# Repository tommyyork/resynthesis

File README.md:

# Resynthesis

This example implements a resynthesis effect for the Electro-Smith Daisy Patch.Init(), initially inspired by [the All Electric Smart Grid project](https://github.com/jvictor0/theallelectricsmartgrid) but it grew towards a granular direction as I added additional processing / while iterating on the output sounds. **This is maybe 90% GPT (🤖), 10% human, so buyer beware if you fork this or use this code.** There are plenty of bugs.

The panel design has most of the development hours, I wanted to procedurally generate it from the KiCad files for Patch.Init():

I've sent this off to the fab, and will make any updates once I've test fitted it on my actual Patch.Init(). Those labels for the pots may be too low...

The panel generation code could pretty easily be adapted to generate panels for any synth module, though the drill diameters and tolerances are currently hardcoded and basically tailored for the jacks / pots / switches you see in many Eurorack modules. The background pattern-to-pattern interpolation... I wish I could take credit. See [the agent session](AGENT_SESSION.md) for the blow by blow on how that came to be.

Incoming audio is analyzed into overlapping FFT grains, processed spectrally (phase propagation, V/OCT pitch, spectral flattening, bright/dark tilt, sparsity, and phase diffusion), and resynthesized with overlap-add back to the output. The V/OCT input (0–10 V) sets the fundamental frequency so the module can be used as an oscillator in a bass patch.

### Offline tests vs hardware signal path

The offline tests under `test/` are designed for **analysis and regressions**, not for level‑matched listening against the live module:

- **V/OCT harmonic tests (`make voct`, `test/test_resynth_voct.cpp`)**  
  - The processed passes are rendered **100% wet** with **no dry mix, no compressor, and no soft clip**.  
  - Grains are normalized only by hop size and active‑grain count, which keeps the **internal DSP stable** but typically yields WAVs that are **much quieter than the dry input**.  
  - This is intentional: the goal is **stable spectra and reliable note detection** (CSV/SVG analysis, suggested‑note checks), not loudness parity with the original sample or with the hardware output.

- **Harmonic engine tests (`make samples` → `test_resynth_harmonic`, `out/harmonic/*.wav`)**  
  - These also run the simplified harmonic resynth engine **fully wet** without the Patch‑SM output chain (no OFFER dry path, no post‑clip compressor, no panel‑driven MAX COMP).  
  - As a result, the harmonic test WAVs can also sit **significantly below** the level of the source material even though the spectra and pitch tracking match the intended behaviour.

- **Hardware firmware (`Resynthesis.cpp`)**  
  - On the Daisy Patch SM, the same core engine is wrapped in a **full output path**: OFFER dry/wet crossfade, hop/overlap‑aware wet gain smoothing, **smoothing‑dependent loudness compensation**, **soft clipping**, and a **fixed compressor/optional MAX COMP** stage.  
  - This chain is where the “finished instrument” loudness lives; the offline tests intentionally **omit** it so they can focus on **spectral behaviour, pitch stability, and CV‑to‑pitch mapping**.

If you A/B the `make voct` / harmonic WAVs against the original samples or the hardware output, expect them to be **significantly quieter**; treat them as **analysis fixtures**, not as loudness‑matched renderings of the module.

## Title: 化 (huà)

The panel uses the single character **化** (*huà*) as its primary title, from the *Daodejing* (道德經) in the sense of **transformation**—the change of one state into another, as in the phrase **化而欲作** (*huà ér yù zuò*, “when transformation arises, desire stirs”; ch. 37). Here it evokes the transformation of incoming sound through the phase vocoder into new timbres and textures.

**Panel typography:** All panel text is set in **all caps** using the open-source DIN-style font **[Gidole](https://github.com/larsenwork/Gidole)** (OFL licence; also available via [Google Fonts](https://fonts.google.com/specimen/Gidole)). The SVG uses the `Gidole` font family with fallbacks (DIN Alternate, DIN 2014, sans-serif) so the panel renders correctly even if Gidole is not installed.

## Make Targets

- **`make` / `make all`**: Build everything for this project (no tests are run): `libDaisy`, `DaisySP`, the `Resynthesis` firmware, host test binaries in `test/`, panel preview PNGs, and the SVG/PDF block‑diagram documentation.
- **`make program`**: Flash the built firmware image to the connected Daisy Patch SM.
- **`make openocd`**: Start OpenOCD for JTAG/SWD debug sessions.
- **`make debug`**: Build a debug firmware image and launch a GDB session against OpenOCD (with logging enabled as described below).
- **`make panel`**: Generate high‑resolution PNG previews of the front‑panel art in `panel/ResynthesisPanel.png` and `panel/ResynthesisPanel_eurorack_overlay.png` (requires Inkscape).
- **`make svg`**: Generate the US Letter block diagram of the audio path in `doc/Resynthesis_BlockDiagram_USLetter.pdf` and `doc/Resynthesis_BlockDiagram_USLetter.svg` (requires Graphviz `dot`).
- **`make test_resynth`**: Build and run the offline V/OCT sweep test; outputs WAVs into `test/out/voct_sweep/`.
- **`make test_cv_sweeps`**: Build and run the CV parameter sweep tests; outputs WAVs into `test/out/cv_sweep/` and `test/out/cv_sweep_maxcomp/`.
- **`make test_panel`**: Run the panel alignment / mechanical checks in `panel/test_panel_alignment.py`.
- **`make tests`**: Run the full test suite (`test_resynth`, `test_cv_sweeps`, and `test_panel`), regenerating WAVs under `test/out/`.
- **`make clean`**: Remove build artifacts and generated assets for this project (host test binaries, `test/out` WAVs, panel PNGs, and block‑diagram PDF/SVG/DOT files).

## Controls and panel mapping

This section is the **source of truth for panel labels and control behaviour**. Labels assume the **default CV bank** (no swapping).

### Potentiometers (CV_1–CV_4)

- **CV_1 – OFFER – send + dry/wet (panel: `OFFER`)**  
  Combined send and mix control for the resynthesis engine. **Fully CCW**, the output is **purely dry input** (non‑pitch‑shifted), and the engine effectively stops seeding new grains, so if no grains are currently active you hear a clean bypass. As you turn toward **12 o’clock**, the input is increasingly **“offered” to the grain engine** while a crossfade brings in the wet signal; around noon you get roughly **half dry, half wet** with the input actively feeding grains. **Fully CW** behaves like a **full send into the resynth path** so the output is dominated by loud, fully wet grains.  
  When **PITCH LOCK is on**, OFFER additionally becomes a **“pitch crossfade”**: CCW you hear the original, unshifted input; CW you hear a **clearly pitched, harmonically focused granular reconstruction** whose fundamental and partials follow the V/OCT voltage and **COLOR** setting, with most of the grain energy collapsing onto those harmonic families. Sweeping OFFER from CCW → CW in this case moves smoothly from dry, unshifted audio into the **fully pitch‑shifted, harmonically reinforced voice**, while existing grains are still allowed to **decay naturally** when you come back toward CCW.

- **CV_2 – Time‑Stretch / Grain Density (panel: `TIMESTRETCH`)**
  Bipolar control around 1× time. This knob controls how quickly grains are launched relative to the analysis hop: **left of centre** slows down and smears the audio into super‑slow, cloud‑like textures, while **right of centre** increases grain density and motion up into fast, chattery clusters. The mapping mirrors the TIME CV input so that the **0 V / noon region** covers the most musically useful 0.25×–4× range, with more extreme slow/fast behaviour toward the ends of travel.

- **CV_3 – FLUFF – granular cloud depth (panel: `FLUFF`)**  
  Sequentially enables a set of increasingly strong “cloud” behaviours in the grains. **Fully CCW** gives the most subtle, stable sound. As you turn clockwise, the engine adds:  
  1. Extra frequency‑dependent phase diffusion on top of CV_8.  
  2. Random jitter of the analysis window within each grain (time smearing) for a denser cloud.  
  3. Micro‑pitch jitter per grain in **pitch‑locked mode** (a few cents of movement around the target note).  
  4. Per‑bin magnitude jitter for a noisy, dense cloud at fully CW.  
  Existing spectral‑energy normalization keeps level changes musical across settings.

- **CV_4 – Color – bright/dark tilt, harmonic & frequency character (panel: `COLOR`)**  
  Three roles:
  - **Spectral tilt:** Negative values darken (emphasize low bins), positive values brighten (emphasize high bins); tilt gain is clamped so extremes do not clip or go silent.  
  - **Harmonic character in both modes (whenever PITCH LOCK is on):** **Color** selects which harmonic family is reinforced in **both** pitch‑locked and partial‑based modes using a **12‑harmonic scaffold** built on the V/OCT fundamental. **Fully CCW** emphasises the **even harmonics** \(2nd, 4th, 6th, … up to 12th\); around **noon** you get a more neutral mix; near **3 o’clock** and beyond the scaffold leans harder into the **odd harmonics**. Power is **front‑loaded into the low harmonics** and then tapered so that roughly the first four harmonics carry most of the added energy and higher harmonics contribute a progressively smaller, more textural sheen. In pitch‑locked mode the scaffold is gentler so the pitched grains stay dominant; in partial‑based mode the scaffold is more forward so simple inputs behave like a full synth voice. Reinforced partials use moderate, tapered gains so they **blend with the resynthesized body** rather than sounding like separate oscillators.  
  - **Pitch vs frequency shifting crossfade:** With PITCH LOCK on, the audio now passes through a dedicated **shifting block** immediately after the input. This block first **detects the incoming pitch** using a harmonic‑comb analyser (refactored from the offline V/OCT tests) and **pitch‑shifts** the input so its fundamental lands on the V/OCT‑selected note *before* any phase‑vocoder processing. As COLOR moves from roughly **3 o’clock to fully CW**, the block smoothly **fades from this pitch‑shifting process into a Bode‑style frequency shifter** whose shift rate also follows V/OCT. Fully CW gives a distinctly **frequency‑shifted, sideband‑style texture** feeding the resynth engine; backing off toward 3 o’clock restores more of the classic pitch‑locked behaviour.

### Toggles (B_7, B_8)

- **B_8 – PITCH LOCK (panel: `PITCH` / `LOCK`)**  
  Mode switch between **pitch‑locked grains** and a **partial‑based spectral model**:
  - **B_8 off – Partial‑based / spectral model mode**: Treats the incoming spectrum as a timbral template. Analysis bins stay at their original pitch; a **harmonic scaffold** (fundamental + harmonics) tuned to the **V/OCT** fundamental is overlaid with moderate gain so simple inputs behave like a full synth voice. **Color (CV_4)** selects the balance of odd vs even harmonics.  
  - **B_8 on – Pitch‑locked grains**: The phase‑vocoder pitch shifter locks each grain so its spectrum follows the V/OCT fundamental. This behaves more like a traditional pitched oscillator with the input acting as a complex waveform; the **same harmonic scaffold** is now applied more gently on top, reinforcing the chosen harmonic family without overwhelming the pitch‑corrected grains.

- **B_7 – MAX COMP (panel: `MAX` / `COMP`)**  
  Toggles a **stronger “MAX COMP” output compressor** after the resynth engine:
  - **Hardware:** B_7 is a **momentary pushbutton**, but the firmware treats it as a **software toggle**: each press flips the MAX COMP state between off and on.  
  - **B_7 off – Normal compression**: A gentle **2:1 feedforward compressor** (threshold ≈ -12 dB, modest make‑up gain) keeps levels musical and consistent as a sound source without being too squashy.  
  - **B_7 on – MAX COMP**: A more aggressive **Omnipressor‑style setting** (negative ratio, higher make‑up gain) that keeps average loudness high and brings out quiet material; this matches the “MAX COMP” path used in the offline CV sweep tests (`test/out/cv_sweep_maxcomp/`). When MAX COMP is active, the **front‑panel status LED above the jacks blinks at roughly 1 Hz** to indicate that the software toggle is engaged.

### CV inputs (CV_5–CV_8, middle jack row)

The middle jack row (panel labels above the jacks) is:

- `V/OCT`, `SMOOTH`, `SPARSITY`, *`D`* (diffusion)

Mapped controls:

- **CV_5 – V/OCT (panel: `V/OCT`, 0–10 V, 1 V/oct)**  
  Volt‑per‑octave pitch control. In both modes the algorithm resynthesizes the input around a musical fundamental set by this voltage (e.g. 1 V ≈ 32.7 Hz / C1, 2 V ≈ 65.4 Hz / C2). In **pitch‑locked mode** the new **shifting block** and the phase‑vocoder engine both treat this as the target note: the block first **shifts the raw input** so its detected fundamental lands on the requested V/OCT pitch, and the phase‑vocoder then follows that same fundamental when mapping grains; in **partial‑based mode** the original spectrum stays nearer its analysed pitch while a more forward harmonic scaffold (fundamental + harmonics) is overlaid at the V/OCT frequency.  
  With PITCH LOCK on and OFFER turned up, the combination of the shifting block and harmonic scaffold now **focuses most of the spectral energy into the fundamental and harmonics implied by V/OCT and COLOR** so the result is a **grainy but clearly pitched voice** rather than a diffuse, purely formant‑style texture. At the very top of COLOR, that same V/OCT value instead drives the **frequency‑shift amount** in the Bode‑style shifter, giving inharmonic, sideband‑rich tones feeding the resynth stage. 0 V = C0 (~16.35 Hz); 10 V is internally clamped near the upper range.

- **CV_6 – Magnitude Smoothing (panel: `SMOOTH`, bipolar, -5 V to +5 V)**  
  Controls how quickly spectral magnitudes follow the input. **Low** voltages track transients closely (crisp, articulate); **high** voltages smear dynamics into a pad‑like magnitude envelope. The engine’s **default** smoothing is now around **0.2**, which keeps transients present while still allowing the adaptive smoothing stages to build a stable, cloud‑like body at higher settings.

- **CV_7 – Spectral Sparsity (panel: `SPARSITY`, bipolar, -5 V to +5 V)**  
  Bipolar control mapped to the full **0–1** sparsity range (0 V ≈ 0.5). Lower values keep most bins active and sound fuller; higher values keep only the strongest bins, leading to more pronounced, metallic / ring‑mod‑like spectra, with internal energy preservation so results stay present rather than simply “thin”.

- **CV_8 – Phase Diffusion (panel: italic `D`, bipolar, -5 V to +5 V)**  
  Bipolar control mapped to the full **0–1** diffusion range (0 V ≈ 0.5). Lower values keep phases more coherent (clearer tone); higher values introduce strong randomization for noisy, cloud‑like, frequency‑shift‑ish textures. **FLUFF (CV_3)** can add extra diffusion on top of this control.

### CV outputs (CV_OUT_1, CV_OUT_2)

- **CV_OUT_1 / C10 – THOUGHTS (panel: lightning bolt symbol `⚡`)**  
  CV jack directly beneath the COLOR knob (top‑right of the middle‑switch/jack cluster).  
  - **Signal:** A **chaotic, Brownian‑like CV** that wanders in a musically bounded way between 0–5 V. Its motion becomes **wider and quicker** when the input is loud and harmonically rich, and **slower and more restrained** when the input is quieter and more noise‑like or spectrally flat.  
  - **Construction:** Internally, THOUGHTS is driven by a **logistic‑map–style chaotic system**. Each audio frame, the engine measures both a smoothed spectral‑energy value and a simple **harmonic peakiness metric** (how “spiky” the spectrum is relative to its mean). These two features form an **excitement** value that modulates the chaotic map’s parameter and effective step rate, then the result is centered, range‑scaled by excitement, and gently low‑pass filtered before being mapped to 0–5 V.  
  - **Musical uses:** Because THOUGHTS reacts to both loudness and harmonic structure but with an internal chaotic drift, it behaves as an **interesting, somewhat tangential CV source**: ideal for slowly moving filter cutoffs, effect depths, wavefolder thresholds, or other processors that you want to “breathe” with the resynth texture without being a simple envelope follower. High‑energy, harmonic material produces animated, complex CV excursions; sparse or dark inputs yield smaller, slower meanders that still feel alive.

- **CV_OUT_2 – Grain energy meter + MAX COMP status / LED driver (no dedicated panel label)**  
  Drives the **front‑panel status LED** (row “LED (status)” in the jack/part mapping table) and exposes a **0–5 V envelope of the grain engine’s activity**, with a **MAX COMP blink overlay**:  
  - **Base behaviour (MAX COMP off):** CV_OUT_2 follows the current **grain / spectral energy** of the resynthesis engine, mapped into **0–5 V**. Quiet, sparse material produces a dim LED / low CV; louder, denser inputs push the LED and CV level towards 5 V.  
  - **MAX COMP on (software toggle engaged):** The same grain‑energy envelope continues to drive CV_OUT_2, but a **logic‑style overlay blinks the output at full intensity (~1.5 Hz)** to show that MAX COMP is active. During the “on” phase of the blink the output is forced to **5 V**; during the “off” phase it returns to the underlying grain‑energy level.  
  This output is intended primarily for the on‑panel LED, but you can patch it elsewhere either as a **grain‑energy envelope follower** or as a **MAX COMP activity indicator**. Its behaviour is independent of **THOUGHTS (CV_OUT_1)**, which continues to carry the separate chaotic CV derived from the same internal analysis.

### Jacks: gates, CVs, and audio I/O

Panel jack layout (from top row to bottom row; labels are **over** each jack and centered):

- **Top row** (4 jacks): `B10`, `B9`, `B5`, `B6` — gate inputs/outputs.
- **Middle row** (4 jacks): `V/OCT` (CV_5), *`t`* / TIME (CV_6), `SPARSITY` (CV_7), *`D`* / diffusion (CV_8).
- **Bottom row** (4 jacks): `IN L`, `IN R`, `OUT L`, `OUT R` — stereo audio inputs and outputs. The two middle jacks are also **CV_OUT_1** and **CV_OUT_2** in firmware.

### Stereo inputs and outputs

- **IN L / IN R (bottom row, left two jacks; panel: `IN L`, `IN R`)**  
  Audio inputs mapped to firmware channels `IN_L` and `IN_R`. They feed the analysis stage of the phase vocoder; typical use is a stereo source (e.g. a loop, synth, or external instrument).

- **OUT L / OUT R (bottom row, right two jacks; panel: `OUT L`, `OUT R`)**  
  Audio outputs mapped to firmware channels `OUT_L` and `OUT_R`. Carry the fully processed resynth signal after shaping, overlap‑add synthesis, soft clipping, and final compressor. Useful both as **effect returns** and as a standalone stereo sound source when driven from V/OCT.

## Panel

### Files

- **`panel/output/ResynthesisPanel.svg`**  
  Vector artwork of a 3U x 10HP Eurorack panel: height **128.5 mm**, width **50.8 mm**. All graphics and drill holes are in millimetres. **Generated by** `panel/_deprecated_generate_panel.py` (or `panel/generate_panel_kicad.py`).

- **`panel/output/ResynthesisPanel.jpg`**  
  Single panel preview image for quick visual reference. Generated from `ResynthesisPanel.svg` by `make panel` (requires Inkscape).

- **`panel/output/render_eurorack_overlay.py`**  
  Script that generates an **Eurorack standard overlay** SVG from any panel SVG: green dotted 2HP vertical grid, neon blue dotted rail‑center lines, neon pink (x, y) annotations at each cut center plus panel dimensions.

- **`panel/_deprecated_generate_panel.py`**  
  Deprecated Python script that generates the canonical `ResynthesisPanel.svg` (prefer `panel/generate_panel_kicad.py`). It encodes the full 3U × 10HP geometry, background artwork, all drill centres, the SD card holder cutout, and the four rectangular Eurorack mounting screw slots so they line up with the Doepfer / Gie‑Tec rail standard (3 mm from the top and bottom edges; see `panel/eurorack_spec/README.md`).

### Input / jack mapping (KiCad PCB → panel)

The table below ties together the **Resynthesis panel labels**, the **Patch.Init default panel silkscreen**, the **KiCad schematic references**, and the mechanical information from the KiCad footprints. Positions are given in KiCad PCB coordinates (millimetres) taken from `panel/KiCad_PCB/ES_Daisy_Patch_SM_FB_Rev1.kicad_pcb`.

| Resynthesis label   | Patch.Init panel label | Component type          | Panel hole Ø (mm) | PCB X (mm) | PCB Y (mm) | KiCad schematic ref | Footprint filename                  |
|---------------------|------------------------|-------------------------|-------------------|------------|------------|----------------------|-------------------------------------|
| B10 (gate in 1)     | B10                    | S_JACK                  | 6.2               | 130.251    | 125.316    | J_GATEIN1            | `S_JACK.kicad_mod`                  |
| B9 (gate in 2)      | B9                     | S_JACK                  | 6.2               | 142.418    | 125.316    | J_GATEIN2            | `S_JACK.kicad_mod`                  |
| B5 (gate out 1)     | B5                     | S_JACK                  | 6.2               | 154.584    | 125.316    | J_GATEOUT1           | `S_JACK.kicad_mod`                  |
| B6 (gate out 2)     | B6                     | S_JACK                  | 6.2               | 166.751    | 125.316    | J_GATEOUT2           | `S_JACK.kicad_mod`                  |
| V/OCT               | CV_5                   | S_JACK                  | 6.2               | 130.251    | 139.065    | J_CV1                | `S_JACK.kicad_mod`                  |
| SMOOTH              | CV_6                   | S_JACK                  | 6.2               | 142.418    | 139.065    | J_CV2                | `S_JACK.kicad_mod`                  |
| SPARSITY            | CV_7                   | S_JACK                  | 6.2               | 154.584    | 139.065    | J_CV3                | `S_JACK.kicad_mod`                  |
| D (diffusion)       | CV_8                   | S_JACK                  | 6.2               | 166.751    | 139.065    | J_CV4                | `S_JACK.kicad_mod`                  |
| IN L                | IN_L / B4              | S_JACK                  | 6.2               | 130.251    | 152.654    | J_LIN1               | `S_JACK.kicad_mod`                  |
| IN R                | IN_R / B3              | S_JACK                  | 6.2               | 142.418    | 152.654    | J_RIN1               | `S_JACK.kicad_mod`                  |
| OUT L               | OUT_L / B2             | S_JACK                  | 6.2               | 154.584    | 152.654    | J_LOUT1              | `S_JACK.kicad_mod`                  |
| OUT R               | OUT_R / B1             | S_JACK                  | 6.2               | 166.751    | 152.654    | J_ROUT1              | `S_JACK.kicad_mod`                  |
| THOUGHTS            | CV_OUT_1 / C10         | S_JACK                  | 6.2               | 165.251    | 100.036    | J_CVOUT1             | `S_JACK.kicad_mod`                  |
| LED (status)        | LED_1                  | LED                     | 3.2               | 148.501    | 60.128     | LED_1                | `LED.kicad_mod`                     |
| MAX COMP (B_7)      | B7 / SW_1              | TL1105SPF250Q_SILK      | 5.5               | 131.751    | 100.036    | SW_1                 | `TL1105SPF250Q_SILK.kicad_mod`      |
| PITCH LOCK (B_8)    | B8 / SW_2              | TOGGLE_ON-ON            | 6.2               | 148.501    | 102.786    | SW_2                 | `TOGGLE_ON-ON.kicad_mod`            |
| microSD slot        | —                      | VERT_MICROSD_CENTERED   | — (rectangular cutout) | 148.501    | 80.855     | U_SDCARD1            | `VERT_MICROSD_CENTERED.kicad_mod`   |
| OFFER (CV_1)        | CV_1 / C5              | 9MM_SNAP-IN_POT_SILK    | 7.2               | 134.251    | 63.756     | VR_1                 | `9MM_SNAP-IN_POT_SILK.kicad_mod`    |
| SMOOTH (CV_2)       | CV_2 / C4              | 9MM_SNAP-IN_POT_SILK    | 7.2               | 162.751    | 63.756     | VR_2                 | `9MM_SNAP-IN_POT_SILK.kicad_mod`    |
| FLUFF (CV_3)        | CV_3 / C3              | 9MM_SNAP-IN_POT_SILK    | 7.2               | 134.251    | 82.865     | VR_3                 | `9MM_SNAP-IN_POT_SILK.kicad_mod`    |
| COLOR (CV_4)        | CV_4 / C2              | 9MM_SNAP-IN_POT_SILK    | 7.2               | 162.751    | 82.865     | VR_4                 | `9MM_SNAP-IN_POT_SILK.kicad_mod`    |

For all jacks, the panel hole diameter is derived from the **S_JACK** KiCad footprint by measuring the outer silkscreen circle at the footprint origin, which reflects the mechanical body / shaft size of the jack that the panel must clear.

### Manufacturing notes

- The SVG uses **mm** for size and coordinates. Most PCB CAD tools can import this as a mechanical layer to generate Gerbers for:
  - Board outline (the outer rectangle)
  - Drill holes (circle centres and radii for jacks, knobs, switches, and mounting holes)
  - **SD card holder cutout** (rectangular cutout matching Patch.Init Edge_Cuts)
  - Silkscreen (text and decorative shapes)
- For a PCB front panel:
  - Use at least **1.6 mm** FR4 for stiffness (or thicker if desired).
  - Put the artwork on the **front silkscreen** and any copper artwork on the **front copper** layers as desired.
  - Make sure to align the drill centres with your chosen hardware footprints (jacks, pots, switches) in your CAD tool before fabrication.

### Panel drill alignment and tests

Earlier iterations of this panel were laid out by eye against the hardware, which meant the **drill locations and diameters did not exactly match** the stock Electrosmith Patch.Init front panel.

The current `panel/ResynthesisPanel.svg` has been revised so that:

- The board outline is **50.8 × 128.5 mm** (10HP × 3U), matching `panel/patch_init_gerbers/blank-Edge_Cuts.gbr`.
- There are **exactly 22 drill holes**, matching the non‑plated NPTH tools in `panel/patch_init_gerbers/blank-NPTH.drl`:
  - 2 × 3.0 mm mounting holes (implemented on the panel as four wide rectangular screw slots whose equivalent 3.0 mm drill centres match the Patch.Init NPTH file and sit 3 mm from the top and bottom edges, per the Eurorack rail standard),
  - 1 × 3.2 mm (T2) for the front‑panel status LED,
- 1 × 5.5 mm (T3) for the **TL1105… / TOGGLE_ON‑ON** toggle switch at B_7 (MAX COMP),
  and 1 × 6.2 mm (sharing the jack-family tool) for the PITCH LOCK toggle at B_8,
  - 1 × 6.2 mm (T4) for the **TL1105… / TOGGLE_ON‑ON** toggle switch at B_8 (PITCH LOCK), sharing the jack-family diameter for additional clearance,
  - 13 × 6.2 mm (T4) for **S_JACK…** audio/CV jacks and gate I/O,
  - 4 × 7.2 mm (T5) for **9MM_SNAP‑IN_POT…** potentiometer shafts.
- A rectangular **SD card holder cutout** is present and matches `panel/patch_init_gerbers/blank-Edge_Cuts.gbr` (position and size within 0.1 mm).
- Hole positions are matched within **0.05 mm** to the NPTH drill file. The **final panel hole diameters** for pots (9MM_SNAP‑IN_POT…), switches (TL1105… / TOGGLE_ON‑ON at B_7 and the PITCH LOCK toggle at B_8), and jacks (S_JACK…) are derived in `panel/_deprecated_generate_panel.py` (and `panel/generate_panel_kicad.py`) from the NPTH drill diameters in `blank-NPTH.drl`, with a small per‑family clearance so the checked‑in artwork (7.5 mm pots, 5.5 mm B_7 switch, 6.3 mm jacks/B_8 switch) remains the single source of truth for the cut‑out geometry while still tracking any future changes to the drill file. The PITCH LOCK / B_8 toggle uses the jack-family 6.2 mm drill (T4) for its panel cutout so the white outline ring encircles the full clearance hole.

The helper script `panel/test_panel_alignment.py` enforces that any panel design passes the tests. Key tests:

- **`test_panel_drill_holes_match_patch_init`** – Verifies that the canonical panel SVG has drill hole positions and diameters identical to `blank-NPTH.drl` (tight tolerances).  
- **`test_custom_panels_align_with_canonical`** – Any alternate `ResynthesisPanel_*.svg` must share the same hardware hole layout as the canonical panel.  
- **`test_canonical_panel_dimensions_and_diameters`** – Checks dimensions, viewBox, and internal consistency of hole radii; confirms Patch.Init PTH drill file is metric.  
- **`test_panel_cutouts_four_pots_switches_and_sd_slot_match_patch_init`** – Confirms pot, switch, and SD‑slot cutouts are present and aligned with the Patch.Init module.  
- **`test_screw_holes_eurorack_rail_distance`** – Verifies that rectangular screw slots are 3 mm from top and bottom edges (Eurorack rails).  
- **`test_panel_passes_pcbway_style_validation`** – Runs PCBWay‑style mechanical checks (min hole size, spacing, hole‑to‑edge, board dimensions).  
- **`test_knob_labels_not_obscured_by_rogan_knobs`** – Ensures Rogan‑style knobs (12 mm) with 0.5 mm clearance do not cover the primary labels (`DRY / WET`, `SMOOTH`, `FLUFF`, `BRIGHT /`).  
- **`test_no_overlapping_text`**, **`test_text_within_printed_area`**, **`test_no_font_smaller_than_10pt`**, **`test_labels_beneath_drill_centered`** – Typography/layout guards so the panel remains legible and mechanically sane.

### External references and expected file formats

External mechanical references and design rules:

- **Eurorack / Doepfer A-100 mechanical standard** – summarized in `panel/eurorack_spec/README.md` (mounting hole positions, panel height, links to Doepfer and other docs).  
- **Patch.Init blank front‑panel Gerbers** – including `blank-NPTH.drl` and `blank-Edge_Cuts.gbr`, used as the mechanical reference.  
- **PCBWay design‑rule documentation** – sets conservative minimums for hole size, spacing, and hole‑to‑edge clearance, as enforced by the tests.

## Instructions

1. **Initialize submodules**:
   ```bash
   git submodule update --init --recursive
   ```
2. **Build the project (normal / release)**:
   ```bash
   make
   ```
3. **Program the device (optional)**:
   ```bash
   make program
   ```

4. **Debug build with JTAG/serial logging (optional)**:
   - Start OpenOCD in one terminal:
     ```bash
     make openocd
     ```
   - In another terminal, build and start a debug session:
     ```bash
     make debug
     ```
   In debug builds the firmware enables Daisy’s logger and:
   - Prints the startup values of all CV_1–CV_8 inputs and the states of switches B_7 and B_8.
   - Periodically prints diagnostic information while audio runs (active grains, spectral energy, current control values, etc.) over the JTAG/serial link.

5. **Run offline V/OCT sample render (optional)**:
   - **Purpose:** The test runs the phase vocoder resynthesis so that the **output length equals the duration of the V/OCT CV movement**: **14 quarter notes at 120 BPM** (7 seconds). The input is truncated or zero-padded to exactly that length. A simulated **V/OCT CV** (0–10 V) steps **once per quarter note** through **two diatonic octaves** (14 steps). **Dry/wet is fixed at 100% wet**. Other parameters use **musical defaults** (smoothing ≈ 0.4, flatten = 0, tilt = 0, sparsity ≈ 0.2, diffusion ≈ 0.2, time scale = 1.0).
   - **Samples:** Place **48 kHz** WAV(s) in `test/samples/`. The test runs for **every WAV** in that folder (no fixed filenames). Outputs go to **`test/out/voct_sweep/`** with names **`<basename>_voct_sweep.wav`** (e.g. `chromaplane_voct_sweep.wav`, `dryseq_voct_sweep.wav`).
  - From the Resynthesis (project) root:
  ```bash
  make samples
  ```
   - **V/OCT CV movement:** The test drives the resynth’s pitch as a volt-per-octave CV (0–10 V) that steps every quarter note at 120 BPM across **two octaves in one pass** (7 s). If you use a sample that requires attribution, add it to the **Attribution** section below.

6. **Run CV parameter sweep renders (optional)**:
   - **Purpose:** For each CV parameter, process the input with that parameter swept across a **musical range of timbres** while the others sit at a slightly bright, low‑sparsity, low‑diffusion “glassy” neutral. Dry/wet is swept 0% → 100% wet **only** in the first test; all other sweeps run at 100% wet. **Default V/OCT is 2 V (C2)** for all sweeps except the V/OCT test. The V/OCT sweep (CV_5) now uses the **sample itself as input** and is **quantized over three octaves (1 V→4 V)** so you hear clear note steps instead of a pure glide. Each set of sweeps is rendered **twice**: once in **pitch‑locked mode** and once in the **partial‑based / spectral‑model mode**. **Four output directories** are used:
     - **`test/out/cv_sweep/`** — CV sweeps **without** MAX COMP in **pitch‑locked mode** (equivalent to **B_7 off** on hardware). One file per parameter per sample: `<basename>_cv1_offer_feed.wav`, `<basename>_cv2_timestretch.wav`, … `<basename>_cv8_phase_diffusion.wav`.
     - **`test/out/cv_sweep_maxcomp/`** — Same sweeps **with** MAX COMP in **pitch‑locked mode** (equivalent to **B_7 on**); each output is checked to have average level **> -60 dBFS**.
     - **`test/out/cv_sweep_partial/`** — CV sweeps **without** MAX COMP in **partial‑based / spectral‑model mode**.
     - **`test/out/cv_sweep_maxcomp_partial/`** — CV sweeps **with** MAX COMP in **partial‑based / spectral‑model mode**.
   - **Samples:** Same as the offline test: **every 48 kHz WAV** in `test/samples/` is processed (e.g. `chromaplane.wav`, `dryseq.wav`). Output names: **`<basename>_cv1_offer_feed.wav`**, **`<basename>_cv2_timestretch.wav`**, **`<basename>_cv3_flatten.wav`**, **`<basename>_cv4_tilt.wav`**, **`<basename>_cv5_voct.wav`** (V/OCT 1 V→4 V over 30 s, sample‑driven and quantized over three octaves), **`<basename>_cv6_smoothing.wav`**, **`<basename>_cv7_sparsity.wav`**, **`<basename>_cv8_phase_diffusion.wav`**. Across the full set of sweeps and both modes, the rendered WAVs move from **clear, glassy resynth tones** at low settings into **harmonically rich, formant‑heavy and cloud‑like textures** at the high end.
  - From the Resynthesis root:
  ```bash
  make samples
  ```

7. **Run FLUFF granular sample renders (optional)**:
   - **Purpose:** Demonstrate how the **FLUFF** control sounds as it is swept across its full range, both with and without V/OCT. For each 48 kHz WAV in `test/samples/`, the test plays the sample **twice**:
     - **First repetition:** FLUFF is swept from **0 → 1** over the length of the sample with **no V/OCT movement** (fixed fundamental, as if the V/OCT jack were unpatched).
     - **Second repetition:** The sample is played again with FLUFF swept **0 → 1** over the second pass while a **diatonic scale from 2 V to 3 V** (one octave, major scale) is spread evenly across the entire length of that second repetition.
   - Outputs go to **`test/out/fluff/`** with names **`<basename>_fluff_sweep.wav`**.
  - From the Resynthesis root:
  ```bash
  make samples
  ```
8. **Run automated property tests (non-audio, recommended for CI)**:
  - **Purpose:** Quickly exercise the core resynthesis engine on synthetic input to guard against obvious stability issues (e.g. NaNs/Infs, gross clipping) without generating WAVs.
  - From the Resynthesis root:
  ```bash
  make tests
  ```

## Design notes for recent DSP changes

- **Smoothing ≈ 0.2 for musicality**: Early versions used ~0.3–0.4 as a neutral smoothing value. After refining the adaptive smoothing curves and loudness compensation, a **lower base smoothing (~0.2)** keeps transients clearer while the activity‑dependent smoothing still builds a stable, pad‑like envelope at higher knob and CV settings. This makes the effect feel more open and less smeared at default, while still reaching glassy extremes when desired.
- **Sparsity and diffusion back to 0–1 (with safeguards)**: The bipolar -5 V..+5 V range now maps to **0–1** for both sparsity and phase diffusion (0 V ≈ 0.5), restoring strong ring‑mod / frequency‑shift‑like metallic effects when desired. Spectral‑energy preservation, grain normalization, and tilt‑gain clamping keep these extremes loud and present rather than simply “thin” or silent.
- **Tilt gain clamping**: The bright/dark tilt originally allowed very large boosts/cuts at the top and bottom of the spectrum, which in practice caused clipping or near‑silence in edge cases (e.g. the `church_bells_cv4_tilt.wav` sweep). Internally, tilt gain is now clamped to a moderate range so full‑scale CV sweeps remain usable while still clearly changing timbre.
- **Spectral energy preservation**: After flatten/tilt/sparsity have been applied in the spectral domain, the total energy is renormalized to closely match the pre‑shaping energy. This reduces level jumps when turning controls and makes the resynth output easier to mix.
- **Grain overlap normalization and soft clip**: Wet grains are normalized by the number of active grains plus hop size so the overall level stays similar whether 1 or several grains overlap. A gentle soft clip on the output catches remaining peaks without harsh distortion, again aiming for a more stable and musical perceived loudness.
- **Fixed compressor (last stage)**: After the soft clip, a feedforward compressor with fixed settings runs so the output is **louder and more consistent** as a sound source for a filter and amplitude (e.g. VCF/VCA). Threshold ≈ -12 dB, ratio 2:1, fast attack (~0.3 ms), medium release (~50 ms), and make-up gain so the resynthesized signal sits at a useful level. This avoids the need to crank downstream gain and evens out dynamics so the module works well as an oscillator or texture source. *Alternative considered:* updating the algorithm so output volume closely follows input volume (e.g. envelope-following gain on the wet path); the compressor was chosen for fixed behaviour, predictable level, and one less dependency on input dynamics.
- **Grain launch jitter (“spray”)**: Grain launch timing is dithered around the nominal hop size (±30%), both on hardware and in the offline / CV sweep tests. This breaks the perfectly regular launch grid so grains overlap in a more scattered, “alien” way while still roughly tracking the requested time‑stretch factor.
-
- **CV sweep timbre coverage (glassy → formant‑heavy)**: The CV sweep tests are voiced so that, taken together, they span a wide range of timbres from **clear, glassy tones** to **harmonically rich, formant‑heavy spectra**:
  - The default sweep “neutral” is slightly bright, low‑sparsity, low‑diffusion, yielding a clean glassy resynth tone when parameters are near their minima.
  - **Smoothing** sweeps from a fast, transient‑friendly value (~0.10) up to a very slow value (~0.95), moving from crisp transient tracking into highly smeared, glass‑like pads.
  - **Flatten** sweeps from a mostly original spectrum (≈0.10) to fully whitened (1.0), making formant peaks and harmonic reinforcement stand out at the high end.
  - **COLOR (tilt) and SPARSITY** sweeps exercise the **harmonic scaffold in both modes**: in pitch‑locked mode the scaffold adds gentle, keyboard‑tracked formants on top of the pitch‑corrected grains; in partial‑based / spectral‑model mode it becomes more dominant, so the odd/even families selected by COLOR produce dense, formant‑style resonances instead of just “thinner” spectra.
  - **Phase diffusion** sweeps from coherent phases (clear tone) to strong diffusion (noisy / cloud‑like textures), with existing energy‑preserving and normalization stages keeping both extremes musically usable in the rendered test WAVs.
- **FLUFF (granular cloud depth)**:
  - The **FLUFF** control is implemented as **four sequential stages**, each adding more granular character while preserving overall level via existing spectral‑energy normalization:
    1. **Extra phase diffusion**: Adds a small, frequency‑dependent phase randomisation on top of CV_8, starting subtly at low FLUFF settings. This softens phase coherence and reduces small pops without washing out the spectrum.
    2. **Analysis‑window jitter**: Shifts each grain’s FFT window slightly forward/backward in the rolling input history. This creates time‑smeared grains and a denser “cloud” from the same source material.
    3. **Micro‑pitch jitter (pitch‑locked mode only)**: In pitch‑locked mode (B_8 on), each grain’s pitch ratio is perturbed by a few cents (amount grows with FLUFF). The result is a shimmering, animated cluster around the nominal V/OCT pitch while remaining clearly in tune.
    4. **Per‑bin magnitude jitter**: At high FLUFF settings, small random gain variations are applied per spectral bin before synthesis (with energy preservation and clamps). This adds a noisy, granular halo to the sound, especially obvious with sustained inputs.

- **Pitch‑locked vs partial‑based modes**: The phase‑vocoder engine exposes a simple mode flag:
- **Pitch‑locked grains (B_8 on):** The global pitch ratio is applied to all bins so grains follow V/OCT directly; a **gentle harmonic scaffold** reinforces the chosen odd/even family from **Color**, keeping the overall feel that of “pitch‑corrected grains with musical formants”. In this mode, with **V/OCT patched and OFFER high**, most grain energy is pulled toward the harmonic series so the sound reads as a **clearly pitched, harmonically rich resynth voice**.
- **Partial‑based / spectral model (B_8 off):** The original spectrum remains at its analysed pitch; a **stronger harmonic bank** tuned to the V/OCT fundamental (with odd/even balance from **Color**) is multiplied into the spectrum, turning simple sources into full, harmonically rich synth voices while still allowing more inharmonic / noisy content to sit between the reinforced partials.

## Attribution (test audio)

The tests use input WAV(s) from `test/samples/`. If you use royalty-free samples that require attribution, add them here. Example for BBC content:

- **Test input sample:** *Church bells* from [BBC Sound Effects](https://sound-effects.bbcrewind.co.uk/), © BBC, used under the [RemArc licence](https://sound-effects.bbcrewind.co.uk/licensing). Used as input to the phase vocoder resynthesis in this project’s test suite.

**Suggested source:** [BBC Sound Effects](https://sound-effects.bbcrewind.co.uk/) — search for “church bells”, “bells”, or “cathedral”; download a clip and convert to 48 kHz WAV if needed. BBC Sound Effects are made available under the [RemArc licence](https://sound-effects.bbcrewind.co.uk/licensing) for personal, educational or research use. Place 48 kHz WAV(s) in `test/samples/`; the tests run for every WAV in that folder.

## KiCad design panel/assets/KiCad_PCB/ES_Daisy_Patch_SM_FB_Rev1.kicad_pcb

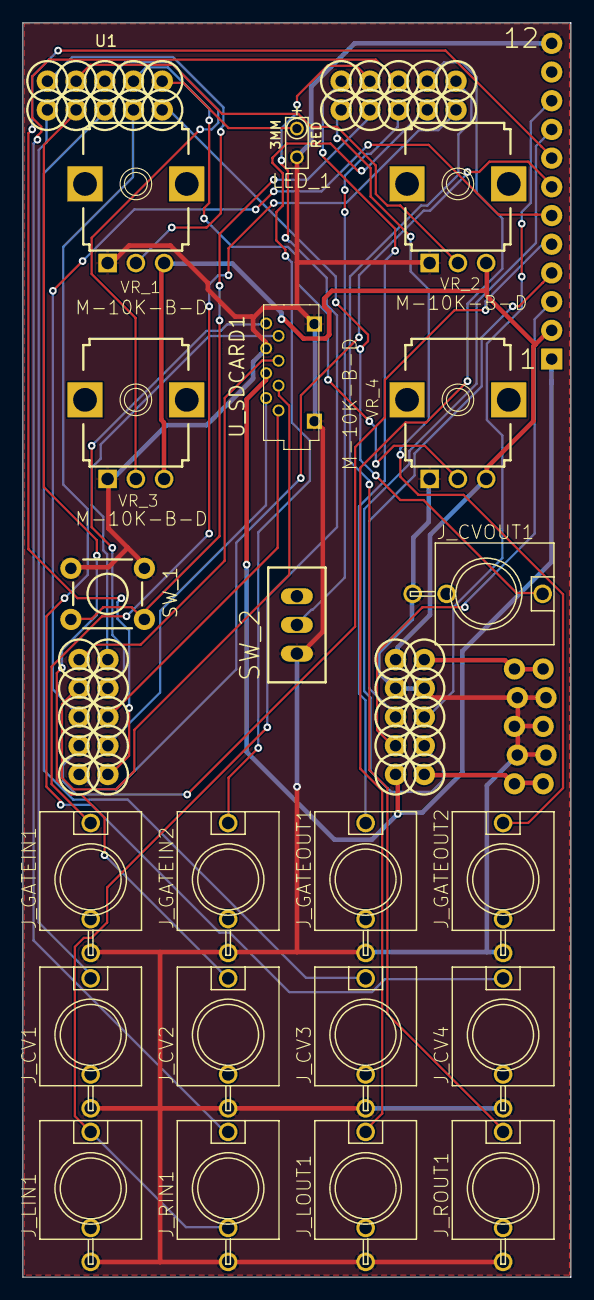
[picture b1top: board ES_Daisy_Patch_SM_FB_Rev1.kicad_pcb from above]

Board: 2 copper layers, 48.5 x 111.0 mm, 26 parts (0 on the bottom side), 39 nets.

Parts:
EP1: EURORACK_POWERLOCK; EURORACK_POWER_SHROUD_LOCK
J_CV1, J_CV2, J_CV3, J_CV4: EURO_JACK; S_JACK
J_CVOUT1: EURO_JACK; S_JACK
J_GATEIN1, J_GATEIN2: EURO_JACK; S_JACK
J_GATEOUT1, J_GATEOUT2: EURO_JACK; S_JACK
J_LIN1: EURO_JACK; S_JACK
J_LOUT1: EURO_JACK; S_JACK
J_RIN1: EURO_JACK; S_JACK
J_ROUT1: EURO_JACK; S_JACK
LED_1: LED
LOGO1: ELECTROSMITH_CIRCLE_4.5MM; ES_CIRCLE_4.5MM
P1: M12; 1X12
SW_1: minibutton; TL1105SPF250Q_SILK
SW_2: TOGGLE_ON-ON
U1: ES_DAISY_PATCH_SM_REV1
U$2: DAISYLOGO; ES_DAISY_LOGO_1
U_SDCARD1: MICRO_SD_CARDCENTERED; VERT_MICROSD_CENTERED
VR_1, VR_2, VR_3, VR_4: M-10K-B-D; 9MM_SNAP-IN_POT_SILK

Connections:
+3V3: P1.1, U1.A10, U_SDCARD1.P$4
+5V: P1.2, U1.A6, VR_1.3, VR_2.3, VR_3.3, VR_4.3
+12V: EP1.POS1, EP1.POS2, U1.A5
-12V: EP1.NEG1, EP1.NEG2, U1.A1
/SD_CK: U1.D6, U_SDCARD1.P$5
/SD_CMD: U1.D7, U_SDCARD1.P$3
/SD_D0: U1.D5, U_SDCARD1.P$7
/SD_D1: U1.D4, U_SDCARD1.P$8
/SD_D2: U1.D3, U_SDCARD1.P$1
/SD_D3: U1.D2, U_SDCARD1.P$2
/SIG_CV1: J_CV1.TIP, U1.C6
/SIG_CV2: J_CV2.TIP, U1.C7
/SIG_CV3: J_CV3.TIP, U1.C8
/SIG_CV4: J_CV4.TIP, U1.C9
/SIG_CVOUT1: J_CVOUT1.TIP, U1.C10
/SIG_CVOUT2: LED_1.A, U1.C1
/SIG_GATE_IN_1: J_GATEIN1.TIP, U1.B10
/SIG_GATE_IN_2: J_GATEIN2.TIP, U1.B9
/SIG_GATE_OUT_1: J_GATEOUT1.TIP, U1.B5
/SIG_GATE_OUT_2: J_GATEOUT2.TIP, U1.B6
/SIG_KNOB1: U1.C5, VR_1.2
/SIG_KNOB2: U1.C4, VR_2.2
/SIG_KNOB3: U1.C3, VR_3.2
/SIG_KNOB4: U1.C2, VR_4.2
/SIG_LIN: J_LIN1.TIP, J_RIN1.NORM, U1.B4
/SIG_LOUT: J_LOUT1.TIP, U1.B2
/SIG_RIN: J_RIN1.TIP, U1.B3
/SIG_ROUT: J_ROUT1.TIP, U1.B1
/SIG_SPI_MISO: P1.6, U1.D8
/SIG_SPI_MOSI: P1.5, U1.D9
/SIG_SPI_NSS: P1.8, U1.D1
/SIG_SPI_SCK: P1.7, U1.D10
/SIG_SW1: SW_1.1, SW_1.2, U1.B7
/SIG_SW2: SW_2.2, U1.B8
/SIG_UART_RX: P1.9, U1.A2
/SIG_UART_TX: P1.10, U1.A3
/SIG_USB_DM: P1.4, U1.A8
/SIG_USB_DP: P1.3, U1.A9
GND: EP1.GND1, EP1.GND2, EP1.GND3, EP1.GND4, EP1.GND5, EP1.GND6, J_CV1.GND, J_CV2.GND, J_CV3.GND, J_CV4.GND, J_CVOUT1.GND, J_GATEIN1.GND, J_GATEIN2.GND, J_GATEOUT1.GND, J_GATEOUT2.GND, J_LIN1.GND, J_LOUT1.GND, J_RIN1.GND, J_ROUT1.GND, LED_1.K, P1.12, SW_1.3, SW_1.4, SW_2.1, U1.A4, U1.A7, U_SDCARD1.GND1, U_SDCARD1.GND2, U_SDCARD1.P$6, VR_1.1, VR_2.1, VR_3.1, VR_4.1

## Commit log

2026-03-05 Resynthesis: adaptive smoothing, MAX COMP routing, and test updates
    - Raise the floor and reshape the CV_2 smoothing response so the panel’s 12 o’clock position is a musical “sweet spot”, concentrating the fastest/grittiest behaviour into the top of the control range.
    - Make magnitude smoothing adaptive to both spectral loudness and harmonic peakiness so dense, excited material automatically smooths into a cloud instead of abrasive static, while simpler inputs rem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
    - Add time‑stretch‑aware smoothing so extreme slow/fast `time_scale` settings get extra smoothing, reducing chatter in `_cv6_timestretch` and related MAX COMP examples without dulling normal operatio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
    -
2026-03-05 Resynthesis: refine sparsity, harmonic stack, and FLUFF renders
    - Tweak spectral sparsity shaping and band‑tilt so high CV values produce more animated, clustered textures while low values behave like gentle density shaping
    - Strengthen V/OCT harmonic scaffold, focusing, and level management so pitched use cases read more clearly without runaway gain
    - Add Makefile fluff target and retune FLUFF test defaults for smoother dynamics and more neutral baseline renders
    Made-with: Cursor
2026-03-05 fix to makefile.
2026-03-05 Resynthesis: retune smoothing and swap TIMESTRETCH/SMOOTH CVs
    Lower default magnitude smoothing to ~0.2, move TIMESTRETCH to CV_2 and SMOOTH to CV_6 across firmware, tests, docs, and panel generator so panel, CV sweeps, and block diagram stay in sync.
    Made-with: Cursor
2026-03-05 Resynthesis: add shifting block and align voct tests
    Add a Shifting front-end that pitch- and frequency-shifts input when PITCH LOCK is on, including a tracking high-pass just below the V/OCT fundamental, and document it in the block diagram and README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
    Made-with: Cursor
2026-03-05 Resynthesis: clarify offline tests and voct stack
    Tie the V/OCT harmonic-stack behaviour more tightly to pitch-locked mode so the requested fundamental dominates suggested-note analysis in the offline voct tests, while keeping the partial-based mode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
    Made-with: Cursor
2026-03-05 Note in the readme that this has moved more granular.
2026-03-06 Refactor - LLM may have screwed up the audio path.
2026-03-06 add taesg as inspiration.
2026-03-07 readme update.
2026-03-07 Panel: KiCad generator, mount slot cap, pattern boundary rules, Makefile
    - Add generate_panel_kicad.py: full KiCad PCB panel generator with three-zone
    pattern (A / morph / B), drill slots, footprints, copper pattern, silkscreen,
    solder mask, and Edge.Cuts. Uses PATTERN_EXTEND outside board and PCBWay DRC
    reference assets.
    - Cap mount drill slot height at 3 mm (MOUNT_SLOT_MAX_HEIGHT_MM); slot width
    unchanged; SD slot uncapped.
2026-03-07 Move pattern SVGs to panel/assets; update AGENT_SESSION.md
    - Relocate panel/pattern.svg, pattern_b.svg, pattern_c.svg to panel/assets/
    - Update generate_panel_kicad.py: PATTERN_SVG and PATTERN_B_SVG now point to
    HERE / 'assets' / 'pattern.svg' and HERE / 'assets' / 'pattern_c.svg'
    - AGENT_SESSION.md: add sections 25 (panel KiCad generator, mount slot cap,
    pattern boundary rules, Makefile) and 26 (SVG move and session log update)
    Made-with: Cursor
2026-03-07 Add kicad render.
2026-03-07 embed render.
2026-03-07 Another quick update.
2026-03-07 fix readme link.
2026-03-07 Last edit, then sleep.
2026-03-07 okay last.
2026-03-08 brand.
2026-03-08 Panel: label-avoiding pattern, bounce off mask, clip to panel, fab-safe output
    Background pattern (generate_panel_kicad.py):
    - Interpolate pattern toward no shape near text label boxes using the same
    easing as zone A→B morph (PATTERN_LABEL_FALLOFF_MM, smoothstep).
    - Terminal points: endpoints stop a random fraction before the label boundary
    (PATTERN_LABEL_TERMINAL_INSET_MIN/MAX) and emit a short arc away in a random
    direction (PATTERN_LABEL_ARC_AWAY_*) so lines do not meet at the center.
